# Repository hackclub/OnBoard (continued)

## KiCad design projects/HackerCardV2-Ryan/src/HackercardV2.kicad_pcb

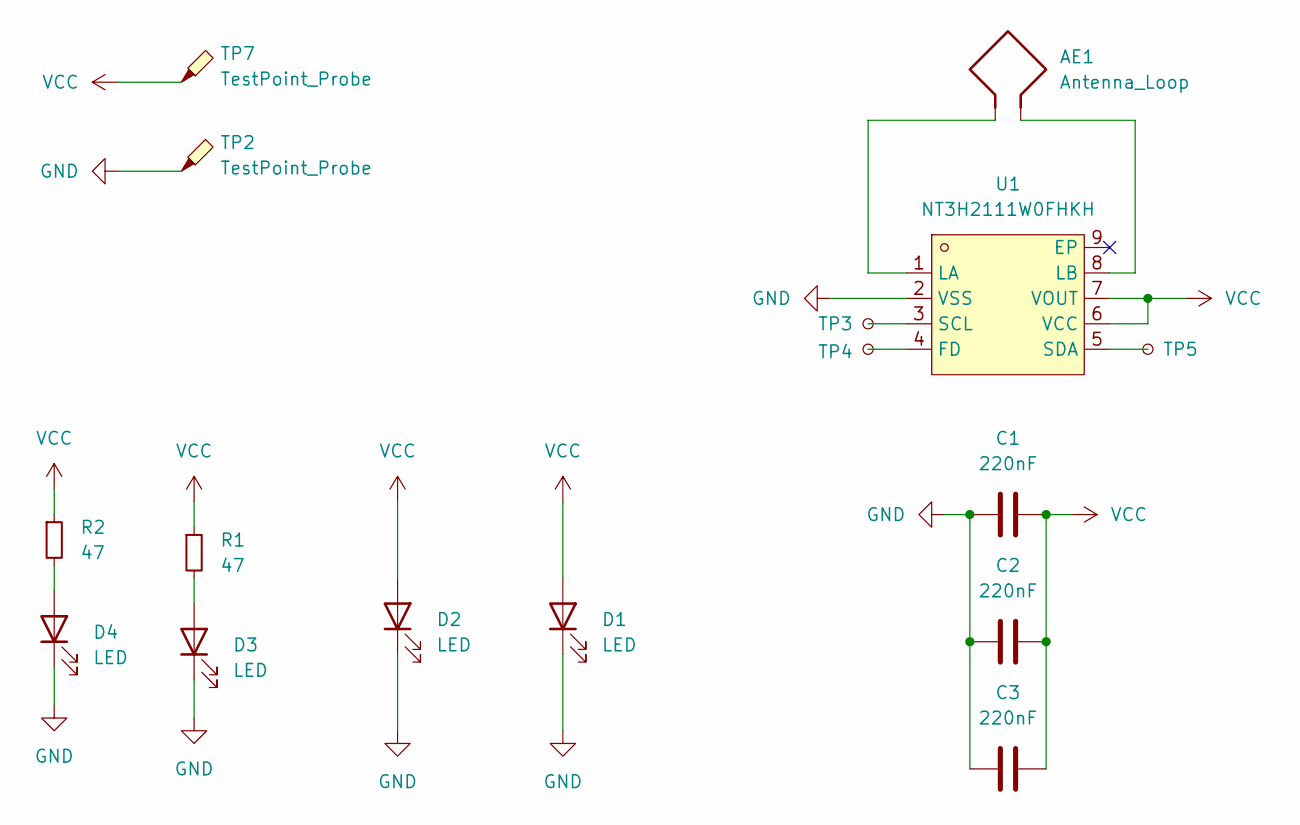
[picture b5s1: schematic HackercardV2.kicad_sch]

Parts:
AE1: Antenna_Loop; nfc-antenna
C1, C2, C3: 220nF; C_0402_1005Metric_Pad0.74x0.62mm_HandSolder
D1, D2, D3, D4: LED; LED_0805_2012Metric_Pad1.15x1.40mm_HandSolder
R1, R2: 47; R_0402_1005Metric_Pad0.72x0.64mm_HandSolder
TP2, TP7: TestPoint_Probe; TestPoint_Loop_D2.54mm_Drill1.5mm_Beaded
TP3, TP4, TP5: TestPoint_Small; TestPoint_Pad_1.0x1.0mm
U1: NT3H2111W0FHKH; XQFN-8_L1.6-W1.6-P0.50-BL; LCSC Part C710403

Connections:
GND: C1.1, C2.1, C3.1, D1.1 (K), D2.1 (K), D3.1 (K), D4.1 (K), TP2.1, U1.2 (VSS)
unnamed: D3.2 (A), R1.2
unnamed: D4.2 (A), R2.2
unnamed: TP4.1, U1.4 (FD)
unnamed: AE1.1, U1.1 (LA)
unnamed: AE1.2, U1.8 (LB)
unnamed: TP3.1, U1.3 (SCL)
unnamed: TP5.1, U1.5 (SDA)
VCC: C1.2, C2.2, C3.2, D1.2 (A), D2.2 (A), R1.1, R2.1, TP7.1, U1.6 (VCC), U1.7 (VOUT)

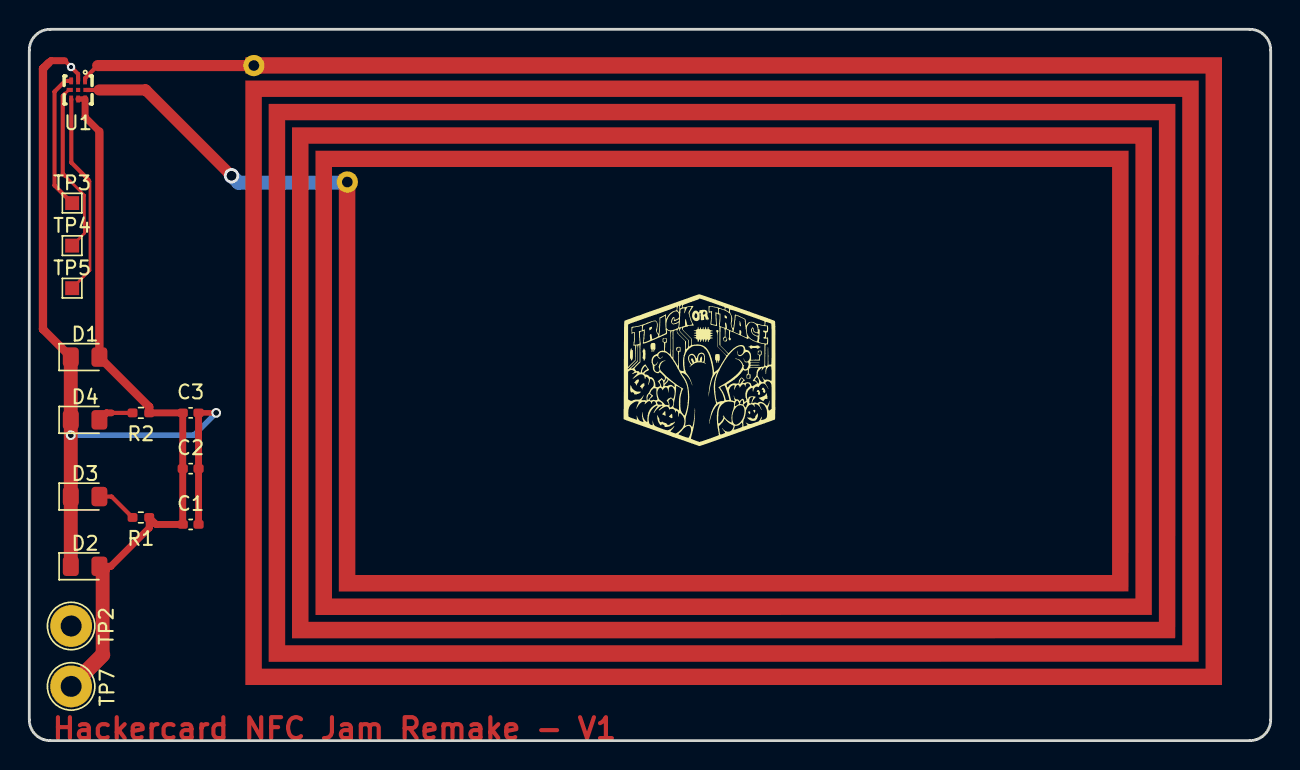
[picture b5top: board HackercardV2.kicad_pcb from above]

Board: 2 copper layers, 89.0 x 51.0 mm, 16 parts (0 on the bottom side), 9 nets.

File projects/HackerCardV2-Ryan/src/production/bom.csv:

Designator,Footprint,Quantity,Value,LCSC Part #
"C1, C2, C3",0603,3,220nF,
"D1, D2, D3, D4",0805,4,LED,
"R1, R2",0603,2,47,
"TP2, TP7",TestPoint_Loop_D2.54mm_Drill1.5mm_Beaded,2,TestPoint_Probe,
"TP3, TP4, TP5",TestPoint_Pad_1.0x1.0mm,3,TestPoint_Small,
U1,XQFN-8_L1.6-W1.6-P0.50-BL,1,NT3H2111W0FHKH,C710403

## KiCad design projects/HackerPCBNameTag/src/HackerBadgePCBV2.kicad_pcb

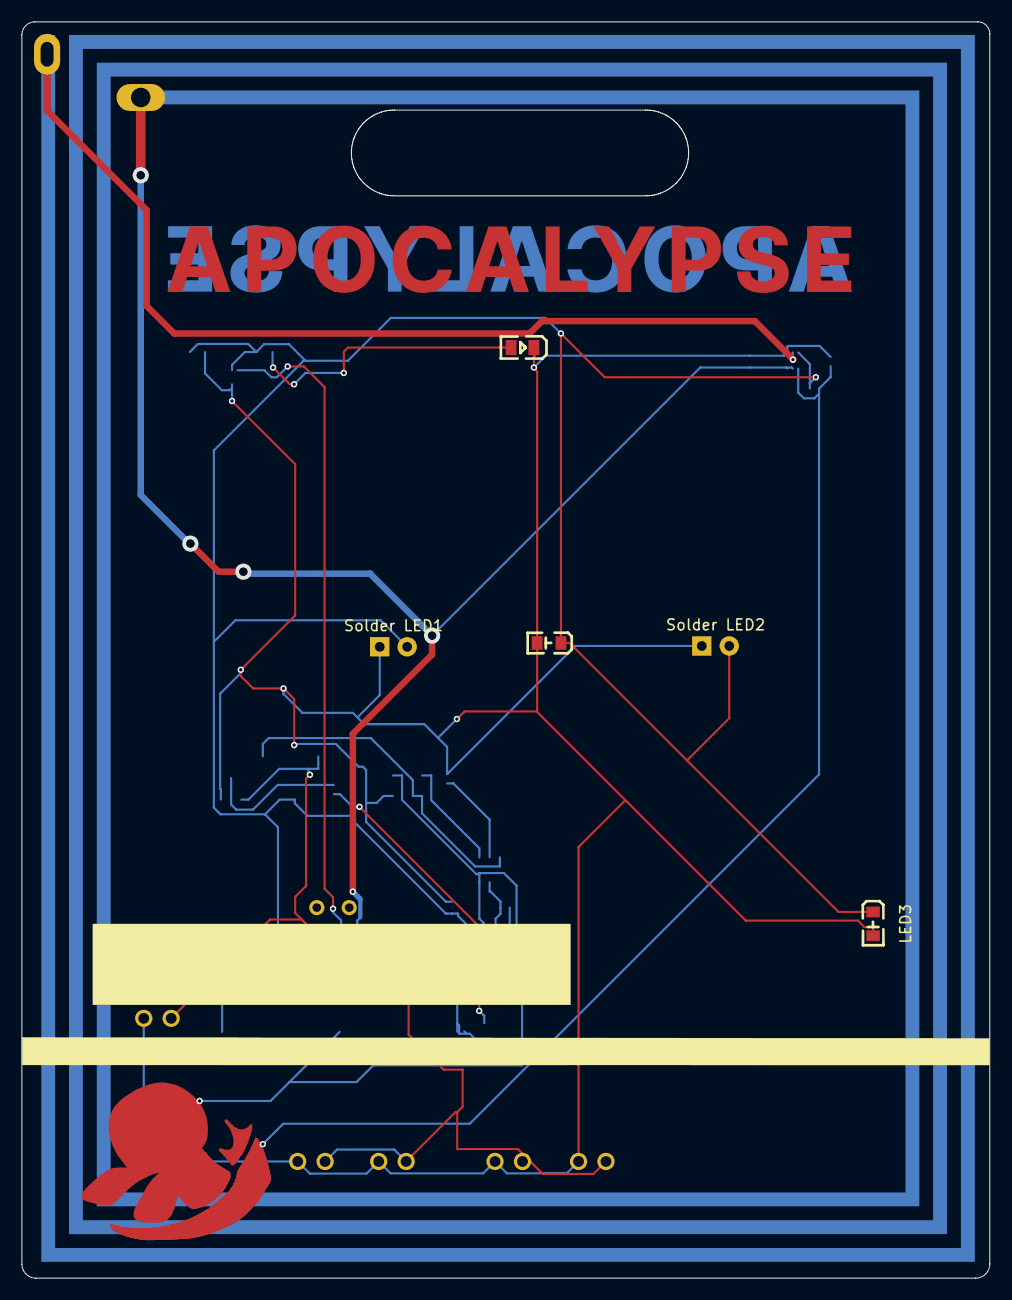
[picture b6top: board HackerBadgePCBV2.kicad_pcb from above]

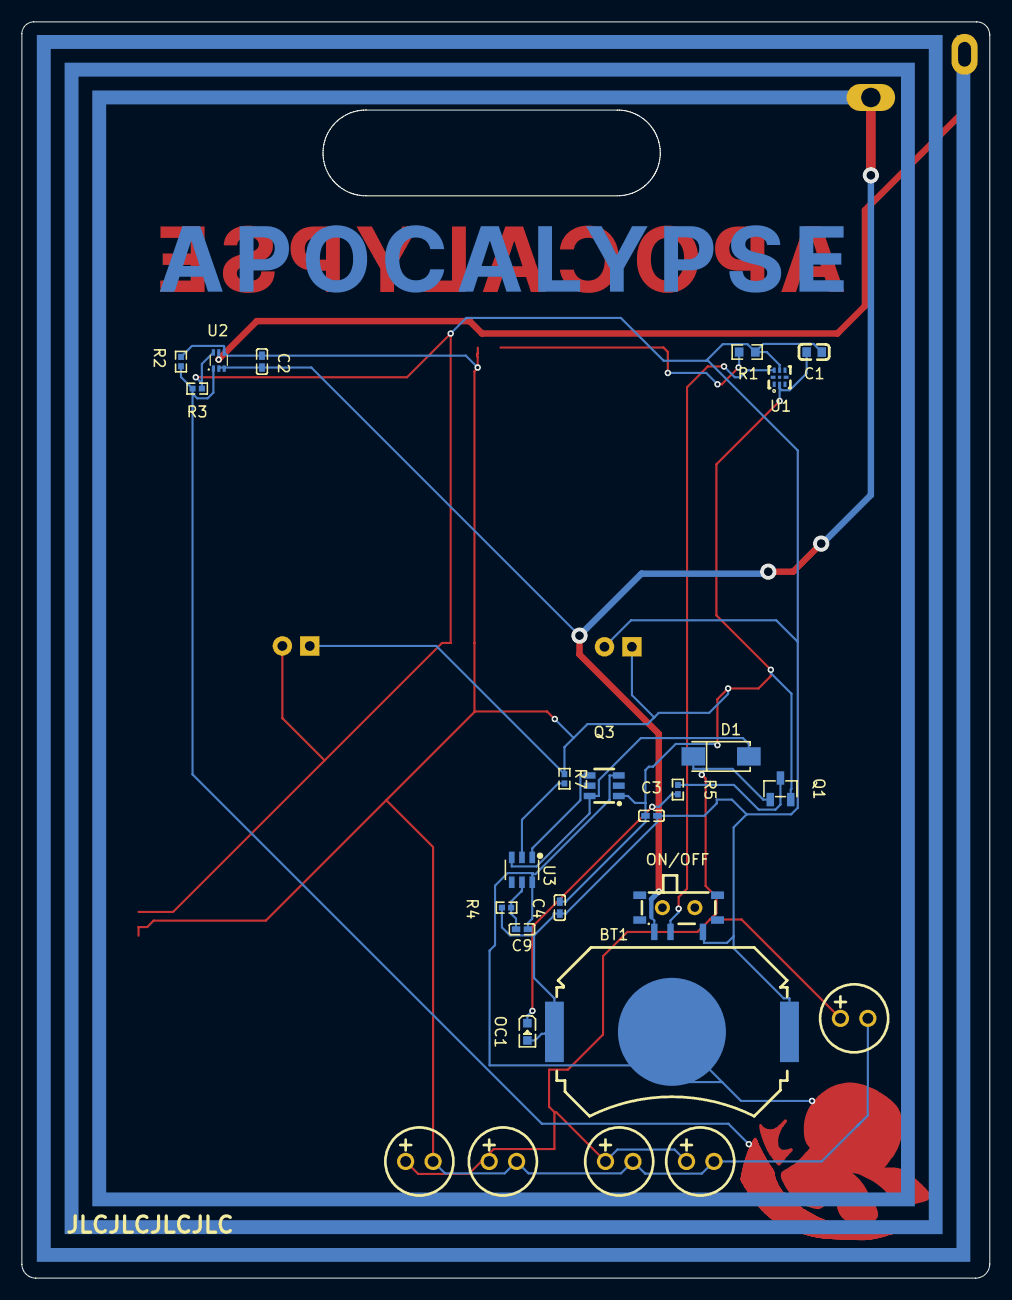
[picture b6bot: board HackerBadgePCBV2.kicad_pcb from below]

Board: 2 copper layers, 89.6 x 116.3 mm, 31 parts (26 on the bottom side), 15 nets.

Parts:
BT1: MY-2032-08; BAT-SMD_MY-2032-08
C1: 220nF; C0603
C2, C3, C9: 100nF; C0402
C4: 10uF; C0402
C5, C6, C7, C8, C10: KF1A221ME050A00CE016; CAP-TH_BD6.3-P2.50-D1.0-FD
D1: SS14; SMA_L4.2-W2.6-LS5.3-RD
L1: 1uH; antenna
LED1: 17-21SUYC/TR8; LED0805-R-RD
LED2, LED3: XL-2835UPC-02; LED0805-RD_GREEN
OC1: KT-0603R; LED0603-RD
ON/OFF: MSK12C02; SW-TH_MSK12C02
Q1: S8050; SOT-23-3_L2.9-W1.3-P1.90-LS2.4-BR
Q3: FS8205A; SOT-23-6_L2.9-W1.6-P0.95-LS2.8-BR
R1: 47Ω; R0603
R2: 200kΩ; R0402
R3: 866kΩ; R0402
R4: 100Ω; R0402
R5: 33Ω; R0402
R7: 1kΩ; R0402
Solder LED1, Solder LED2: LED_Pad; LED_D5.0mm_Horizontal_O6.35mm_Z15.0mm
U1: NT3H2111W0FHKH; XQFN-8_L1.6-W1.6-P0.50-BL
U2: TPS61023DRLR; SOT-563_L1.6-W1.2-P0.50-LS1.6-BR
U3: DW01A_C351410; SOT-23-6_L2.9-W1.6-P0.95-LS2.8-BL

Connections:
/OC: D1.2 (A), Q3.6 (G1), U3.3 (OC)
BAT-: BT1.2, C9.1, Q3.3 (S2), U3.6 (GND)
GND: C1.1, C2.1, C3.1, C4.1, C5.2, C6.2, C7.2, C8.2, C10.2, LED1.2 (-), LED2.2 (K), LED3.2 (K), Q1.2 (E), Q3.1 (S1), R2.1, R7.1, Solder LED1.1 (K), Solder LED2.1 (K), U1.2 (VSS), U2.4 (GND)
unnamed: C5.1, C6.1, C7.1, C8.1, C10.1, D1.1 (K), Q1.1 (B)
unnamed: LED1.1 (+), R1.1
unnamed: OC1.1 (K), R5.2
unnamed: Q1.3 (C), R5.1
unnamed: Q3.4 (G2), U3.1 (OD)
unnamed: ON/OFF.2, U1.7 (VOUT)
unnamed: C2.2, L1.3, ON/OFF.3, U2.2 (EN), U2.3 (VIN)
unnamed: R2.2, R3.1, U2.1 (FB)
unnamed: L1.2, U2.5 (SW)
unnamed: C9.2, R4.1, U3.5 (VCC)
unnamed: R7.2, U3.2 (VM)
VCC: BT1.1, C1.2, C3.2, C4.2, LED2.1 (A), LED3.1 (A), OC1.2 (A), ON/OFF.1, R1.2, R3.2, R4.2, Solder LED1.2 (A), Solder LED2.2 (A), U1.6 (VCC), U2.6 (VOUT)

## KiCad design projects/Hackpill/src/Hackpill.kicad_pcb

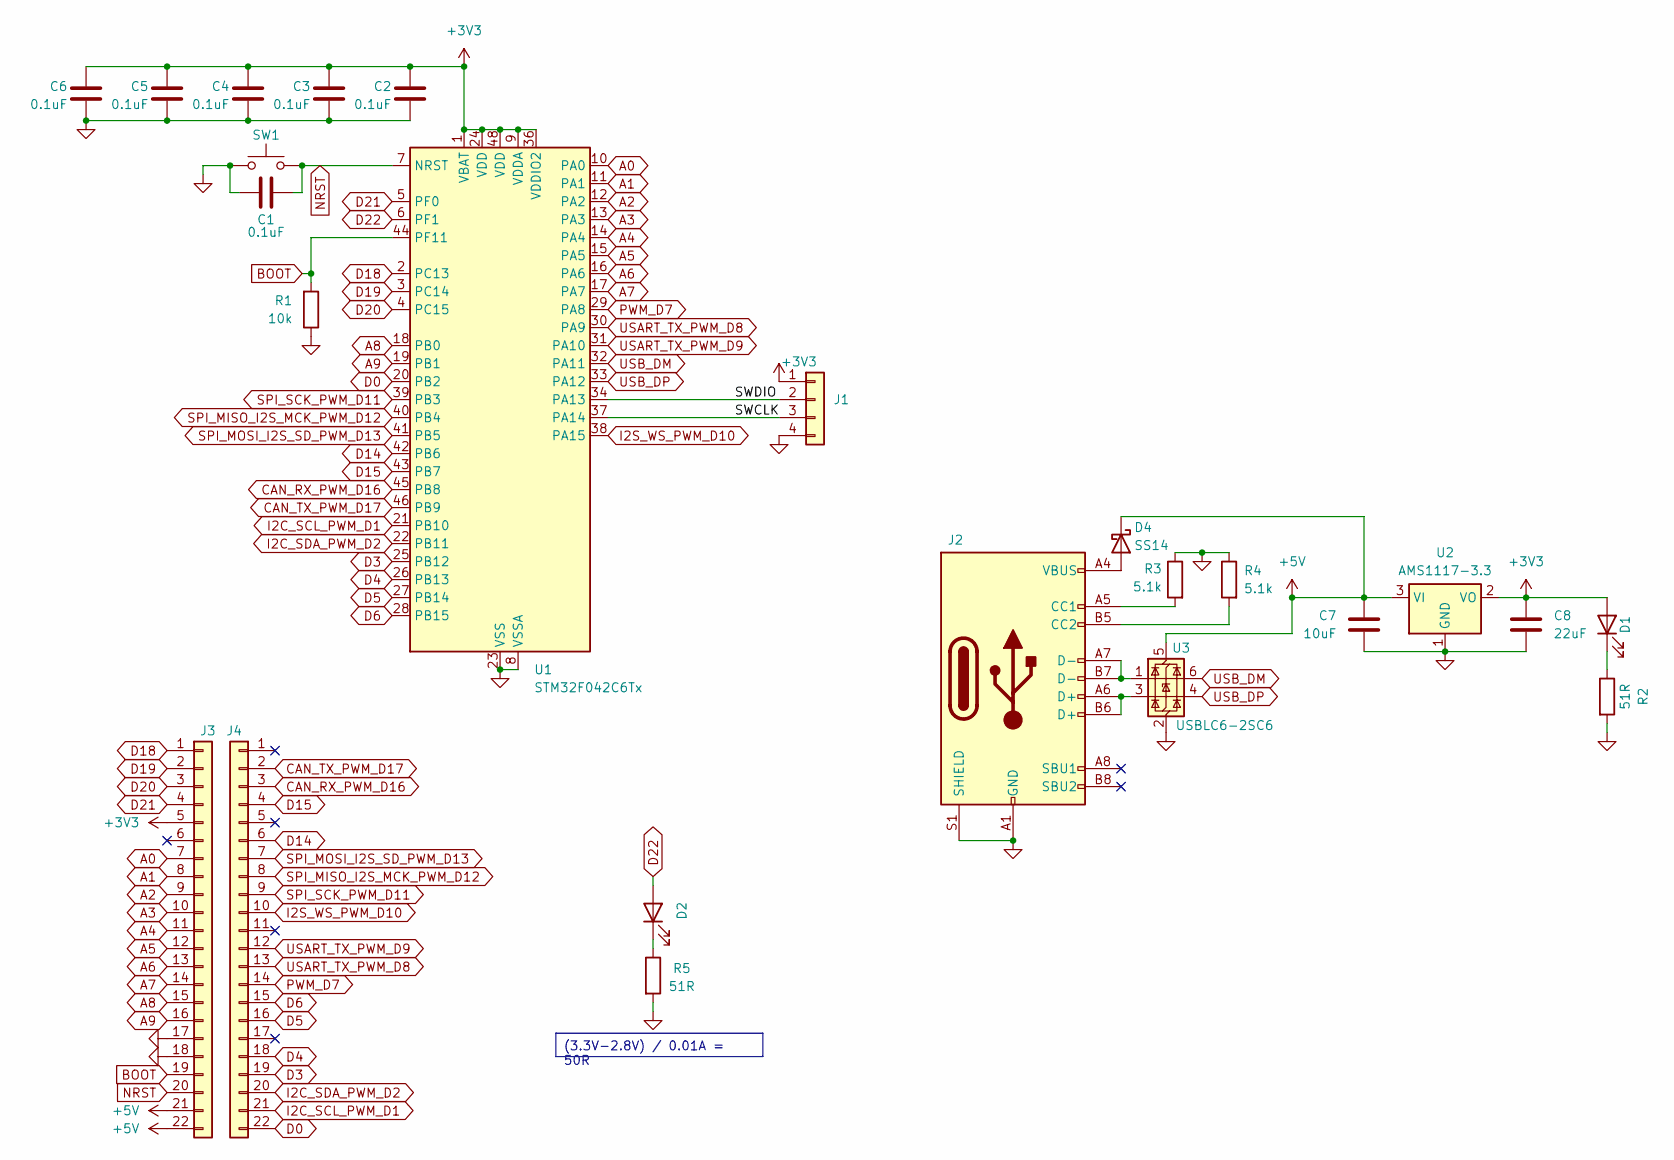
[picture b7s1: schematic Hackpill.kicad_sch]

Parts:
C1, C2, C3, C4, C5, C6: 0.1uF; C_0603_1608Metric
C7: 10uF; C_0603_1608Metric
C8: 22uF; C_0603_1608Metric
D1, D2: LED; LED_0805_2012Metric; LCSC C2297
D4: SS14; D_SMA
J1: Conn_01x04; PinHeader_1x04_P2.54mm_Vertical
J2: USB_C_Receptacle_USB2.0_16P; USB_C_Receptacle_Hanbo_16P_TopMnt_Horizontal; LCSC C6332269
J3, J4: Conn_01x22; PinSocket_1x22_P2.54mm_Vertical
R1: 10k; R_0603_1608Metric
R2, R5: 51R; R_0603_1608Metric
R3, R4: 5.1k; R_0603_1608Metric
SW1: SW_Push; SW_Push_1P1T_XKB_TS-1187A; LCSC C318884
U1: STM32F042C6Tx; LQFP-48_7x7mm_P0.5mm; LCSC C88447
U2: AMS1117-3.3; SOT-223-3_TabPin2; LCSC C6186
U3: USBLC6-2SC6; SOT-23-6; LCSC C2827654

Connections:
+3V3: C2.1, C3.1, C4.1, C5.1, C6.1, C8.1, D1.2 (A), J1.1, J3.5, U1.1 (VBAT), U1.9 (VDDA), U1.24 (VDD), U1.36 (VDDIO2), U1.48 (VDD), U2.2 (VO)
+5V: C7.1, D4.1 (K), J3.21, J3.22, U2.3 (VI), U3.5 (VBUS)
/SWCLK: J1.3, U1.37 (PA14)
/SWDIO: J1.2, U1.34 (PA13)
A0: J3.7, U1.10 (PA0)
A1: J3.8, U1.11 (PA1)
A2: J3.9, U1.12 (PA2)
A3: J3.10, U1.13 (PA3)
A4: J3.11, U1.14 (PA4)
A5: J3.12, U1.15 (PA5)
A6: J3.13, U1.16 (PA6)
A7: J3.14, U1.17 (PA7)
A8: J3.15, U1.18 (PB0)
A9: J3.16, U1.19 (PB1)
BOOT: J3.19, R1.2, U1.44 (PF11)
CAN_RX_PWM_D16: J4.3, U1.45 (PB8)
CAN_TX_PWM_D17: J4.2, U1.46 (PB9)
D0: J4.22, U1.20 (PB2)
D3: J4.19, U1.25 (PB12)
D4: J4.18, U1.26 (PB13)
D5: J4.16, U1.27 (PB14)
D6: J4.15, U1.28 (PB15)
D14: J4.6, U1.42 (PB6)
D15: J4.4, U1.43 (PB7)
D18: J3.1, U1.2 (PC13)
D19: J3.2, U1.3 (PC14)
D20: J3.3, U1.4 (PC15)
D21: J3.4, U1.5 (PF0)
D22: D2.2 (A), U1.6 (PF1)
GND: C1.1, C2.2, C3.2, C4.2, C5.2, C6.2, C7.2, C8.2, J1.4, J2.A1 (GND), J2.A12 (GND), J2.B1 (GND), J2.B12 (GND), J2.S1 (SHIELD), J3.17, J3.18, R1.1, R2.2, R3.1, R4.1, R5.2, SW1.1, U1.8 (VSSA), U1.23 (VSS), U1.35 (VSS), U1.47 (VSS), U2.1 (GND), U3.2 (GND)
I2C_SCL_PWM_D1: J4.21, U1.21 (PB10)
I2C_SDA_PWM_D2: J4.20, U1.22 (PB11)
I2S_WS_PWM_D10: J4.10, U1.38 (PA15)
NRST: C1.2, J3.20, SW1.2, U1.7 (NRST)
unnamed: D1.1 (K), R2.1
unnamed: D2.1 (K), R5.1
unnamed: D4.2 (A), J2.A4 (VBUS), J2.A9 (VBUS), J2.B4 (VBUS), J2.B9 (VBUS)
unnamed: J2.A5 (CC1), R3.2
unnamed: J2.B5 (CC2), R4.2
unnamed: J2.A6 (D+), J2.B6 (D+), U3.3 (I/O2)
unnamed: J2.A7 (D-), J2.B7 (D-), U3.1 (I/O1)
PWM_D7: J4.14, U1.29 (PA8)
SPI_MISO_I2S_MCK_PWM_D12: J4.8, U1.40 (PB4)
SPI_MOSI_I2S_SD_PWM_D13: J4.7, U1.41 (PB5)
SPI_SCK_PWM_D11: J4.9, U1.39 (PB3)
USART_TX_PWM_D8: J4.13, U1.30 (PA9)
USART_TX_PWM_D9: J4.12, U1.31 (PA10)
USB_DM: U1.32 (PA11), U3.6 (I/O1)
USB_DP: U1.33 (PA12), U3.4 (I/O2)

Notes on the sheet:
(3.3V-2.8V) / 0.01A = 50R

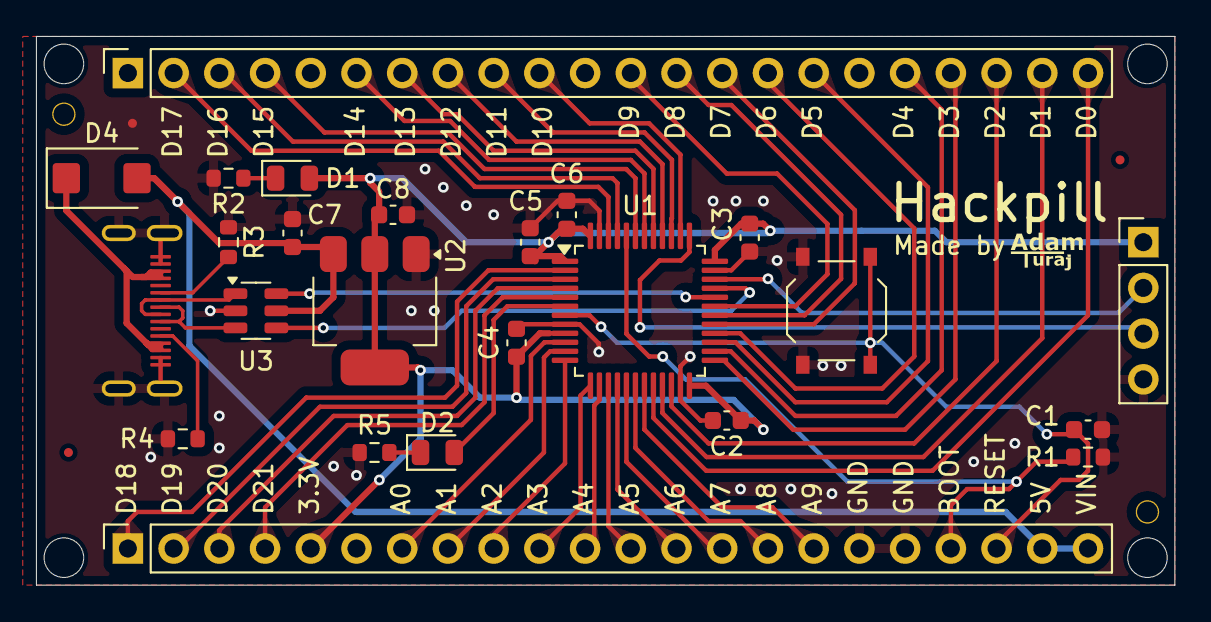
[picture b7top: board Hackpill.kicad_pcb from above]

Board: 2 copper layers, 63.2 x 30.5 mm, 24 parts (0 on the bottom side), 49 nets.
